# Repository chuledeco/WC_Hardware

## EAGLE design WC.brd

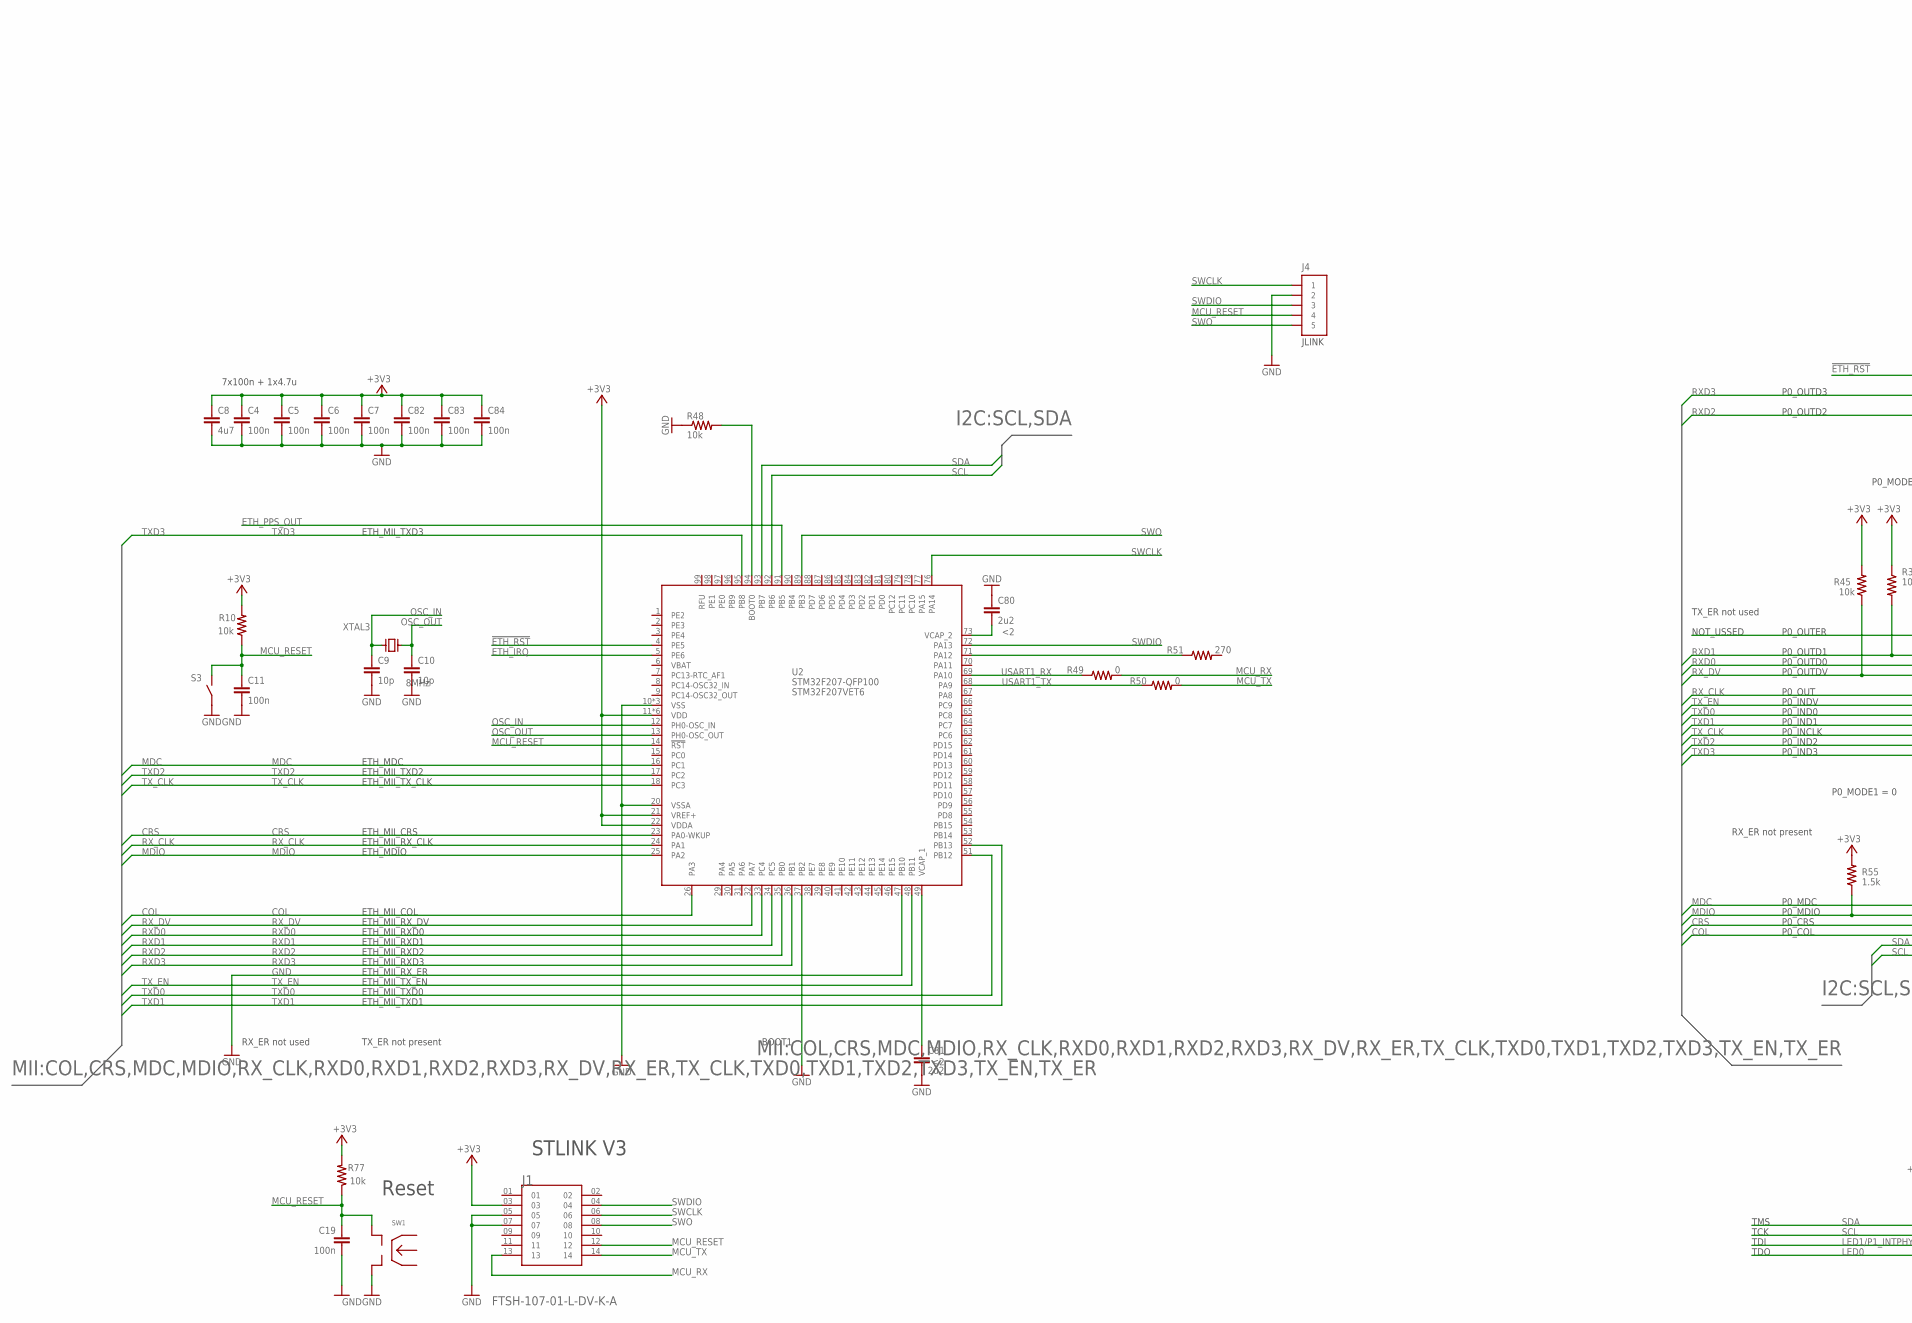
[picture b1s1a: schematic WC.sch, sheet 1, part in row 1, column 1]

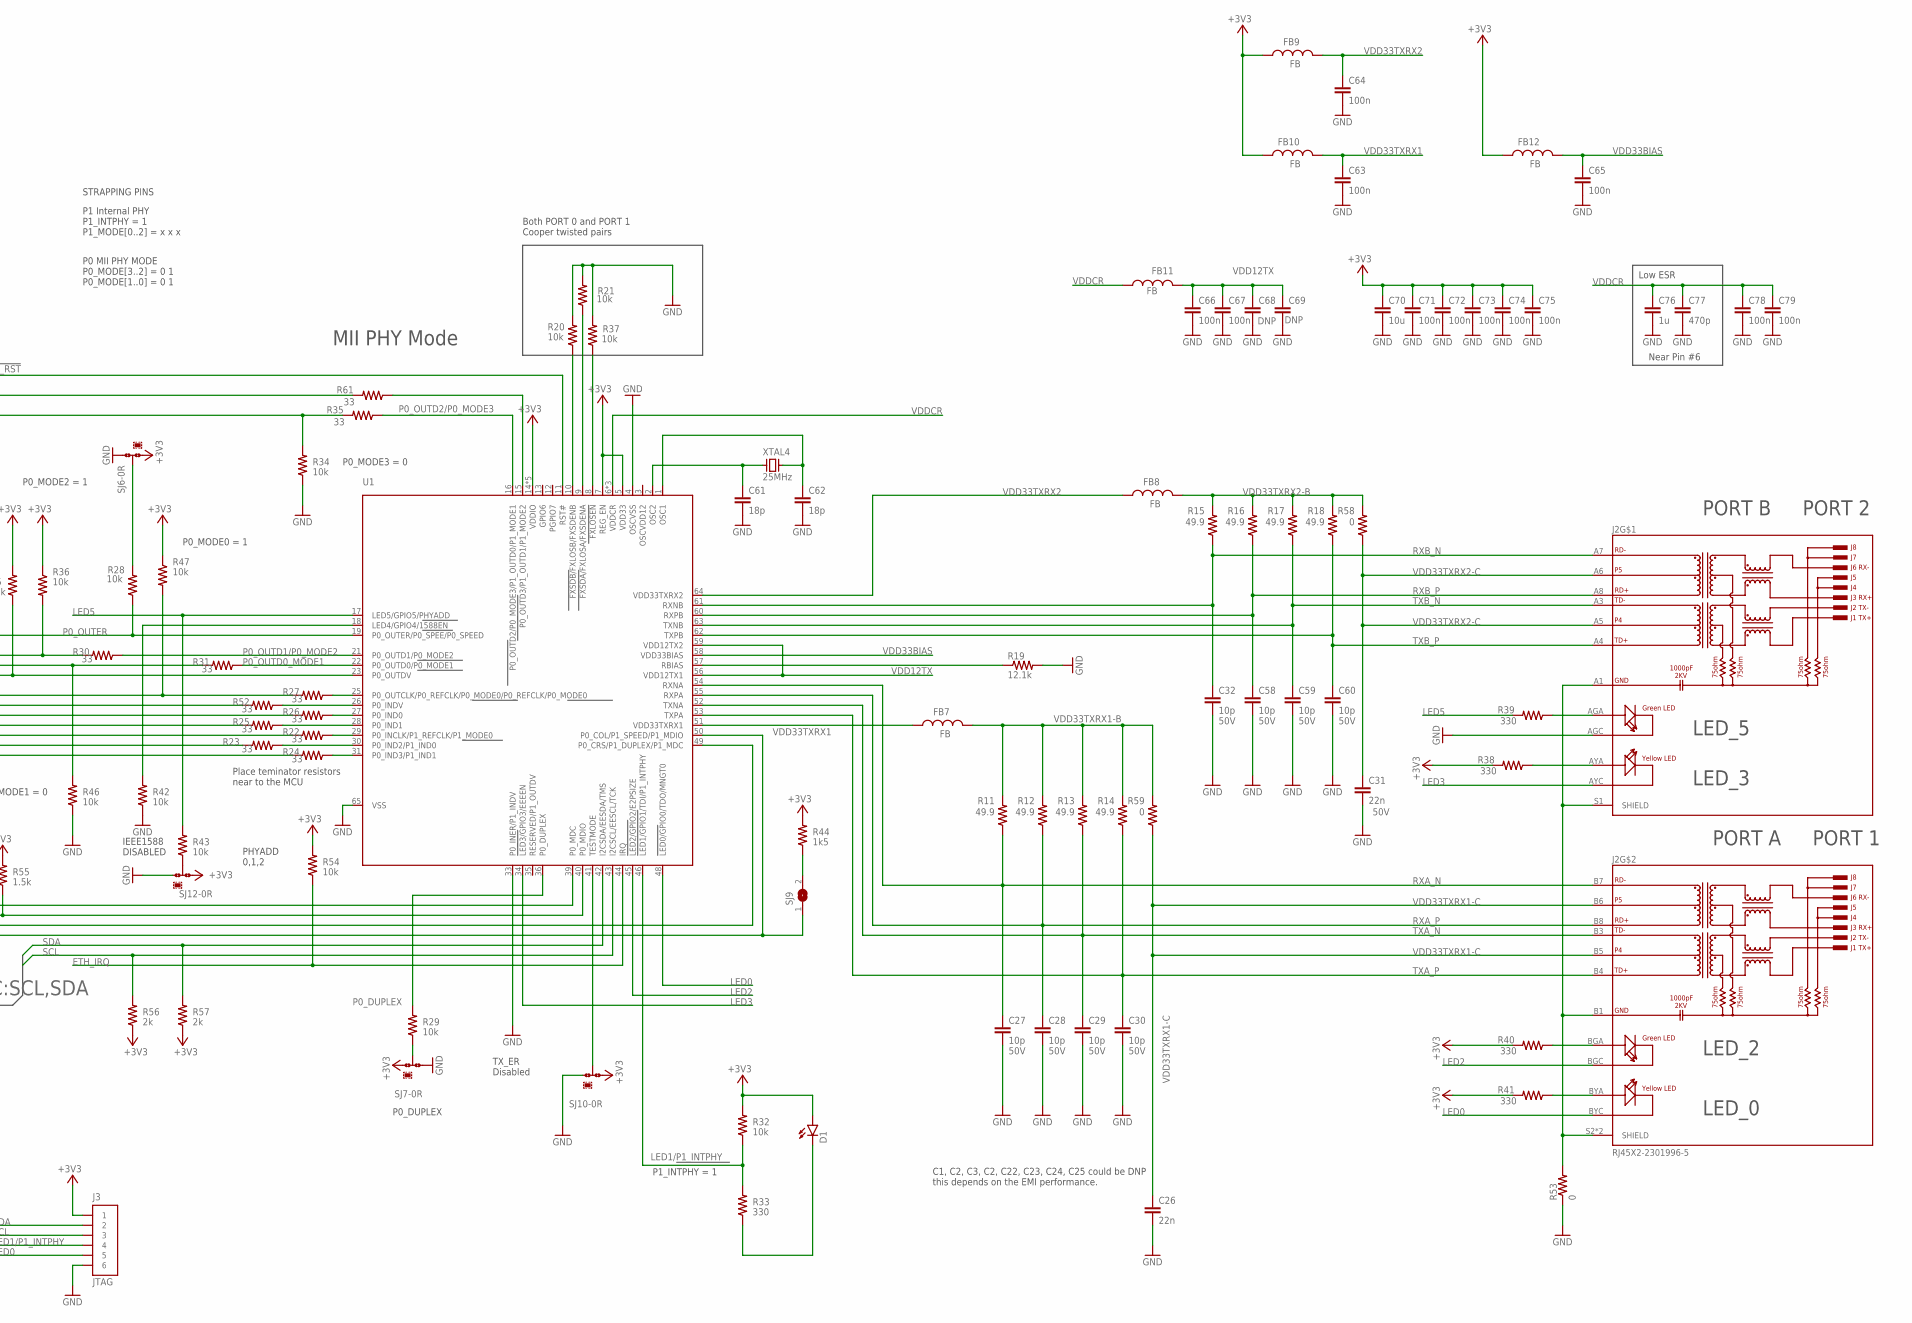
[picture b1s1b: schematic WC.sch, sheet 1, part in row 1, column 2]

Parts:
C4, C5, C6, C7, C11, C19, C63, C64, C65, C66, C67, C68, C69, C71, C72, C73, C74, C75, C78, C79, C82, C83, C84: 100n; C_0603
C8: 4u7; C_0805
C9, C10: 10p; C_0603
C26: 22n; C_0805
C27, C28, C29, C30, C32, C58, C59, C60: 10p; C_0402
C31: 22n; C_0805; VOLTAGE 50V
C61, C62: 18p; C_0603
C70: 10u; C_0603
C76: 1u; C_0603
C77: 470p; C_0603
C80, C81: 2u2; C_0603
D1: LED_0603_ARROW
FB7, FB8, FB9, FB10, FB11, FB12: FB; L_0603
J1: FTSH-107-01-L-DV-K-A; SAMTEC_FTSH-107-01-L-DV-K-A
J2: RJ45X2-2301996-5; 2301996-5
J3: JTAG; CONN-VERT-2.54MM-6PINS-2ROWS
J4: CONVERT-1X5-2.54MM-MALE_HOLES; 1X05
R10, R20, R21, R28, R29, R32, R34, R36, R37, R42, R43, R45, R46, R47, R48, R54, R77: 10k; R_0603
R11, R12, R13, R14, R15, R16, R17, R18: 49.9; R_0402
R19: 12.1k; R_0603
R22, R23, R24, R25, R26, R27, R30, R31, R35, R52, R61: 33; R_0603
R33, R38, R39, R40, R41: 330; R_0603
R44: 1k5; R_0603
R49, R50: 0; R_0603
R51: 270; R_0603
R53: 0; R_1206
R55: 1.5k; R_0603
R56, R57: 2k; R_0603
R58, R59: 0; R_0402
S3: TSWITCH_SMTR2; SMTR2
SJ6: attributre; A0R-JMP
SJ7, SJ10, SJ12: 0R-JUMPA; A0R-JMP
SJ9: SJ
SW1: SWITCH-SCREW; SCREW-SWITCH
U1: LAN9353; QFN50P900X900X100-65T600N
U2: STM32F207-QFP100; QFP50P1600X1600X160-100N; MPN STM32F207VET6
XTAL3: 8MHz; XTAL3.2X2.5; MPN 830108313809
XTAL4: 25MHz; XTAL3.2X2.5

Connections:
!ETH_RST!: U1.11 (RST#), U2.4 (PE5)
+3V3: C4.P$1 (1), C5.P$1 (1), C6.P$1 (1), C7.P$1 (1), C8.P$1 (1), C70.P$1 (1), C71.P$1 (1), C72.P$1 (1), C73.P$1 (1), C74.P$1 (1), C75.P$1 (1), C82.P$1 (1), C83.P$1 (1), C84.P$1 (1), D1.A, FB9.2, FB10.2, FB12.2, J1.03, J3.1, R10.2, R32.2, R36.1, R38.2, R40.2, R41.2, R44.2, R45.2, R47.1, R54.2, R55.2, R56.1, R57.1, R77.2, SJ6.1, SJ7.1, SJ10.3, SJ12.3, U1.5 (VDD33), U1.7 (REG_EN), U1.14 (VDDIO), U1.20 (VDDIO), U1.32 (VDDIO), U1.37 (VDDIO), U1.47 (VDDIO), U2.11 (VDD), U2.19 (VDD), U2.21 (VREF+), U2.22 (VDDA), U2.28 (VDD), U2.50 (VDD), U2.75 (VDD), U2.100 (VDD); also elsewhere on the board
COL: SJ9.1, U1.50 (P0_COL/P1_SPEED/P1_MDIO), U2.26 (PA3)
CRS: U1.49 (P0_CRS/P1_DUPLEX/P1_MDC), U2.23 (PA0-WKUP)
ETH_IRQ: R54.1, U1.44 (IRQ), U2.5 (PE6)
ETH_PPS_OUT: U2.91 (PB5)
GND: C4.P$2 (2), C5.P$2 (2), C6.P$2 (2), C7.P$2 (2), C8.P$2 (2), C9.P$2 (2), C10.P$2 (2), C11.P$2 (2), C19.P$2 (2), C26.P$2 (2), C27.P$2 (2), C28.P$2 (2), C29.P$2 (2), C30.P$2 (2), C31.P$2 (2), C32.P$2 (2), C58.P$2 (2), C59.P$2 (2), C60.P$2 (2), C61.P$2 (2), C62.P$2 (2), C63.P$2 (2), C64.P$2 (2), C65.P$2 (2), C66.P$2 (2), C67.P$2 (2), C68.P$2 (2), C69.P$2 (2), C70.P$2 (2), C71.P$2 (2), C72.P$2 (2), C73.P$2 (2), C74.P$2 (2), C75.P$2 (2), C76.P$2 (2), C77.P$2 (2), C78.P$2 (2), C79.P$2 (2), C80.P$1 (1), C81.P$2 (2), C82.P$2 (2), C83.P$2 (2), C84.P$2 (2), J1.05, J1.07, J2.AGC (GC), J3.6, J4.2, R19.2, R20.2, R21.2, R34.1, R37.2, R42.1, R46.1, R48.1, R53.1, S3.P$1, S3.P$2, SJ6.3, SJ7.3, SJ10.1, SJ12.1, SW1.2, U1.4 (OSCVSS), U1.33 (P0_INER/P1_INDV), U1.65 (VSS), U2.10 (VSS), U2.20 (VSSA), U2.27 (VSS), U2.37 (PB2), U2.47 (PB10), U2.74 (VSS); also elsewhere on the board
LED0: J2.BYC (YC), J3.5, U1.48 (LED0/GPIO0/TDO/MNGT0)
LED1/P1_INTPHY: J3.4, R32.1, R33.2, U1.46 (LED1/GPIO1/TDI/P1_INTPHY)
LED1_C1: D1.K, R33.1
LED2: J2.BGC (GC), U1.45 (LED2/GPIO2/E2PSIZE)
LED3: J2.AYC (YC), U1.34 (LED3/GPIO3/EEEEN)
LED5: R39.2, R43.2, U1.17 (LED5/GPIO5/PHYADD)
MCU_RESET: C11.P$1 (1), C19.P$1 (1), J1.12, J4.4, R10.1, R77.1, S3.P$3, S3.P$4, SW1.1, U2.14 (!RST!)
MCU_RX: J1.13, R49.2
MCU_TX: J1.14, R50.2
MDC: U1.39 (P0_MDC), U2.16 (PC1)
MDIO: R55.1, U1.40 (P0_MDIO), U2.25 (PA2)
unnamed: R43.1, SJ12.2
unnamed: C80.P$2 (2), U2.73 (VCAP_2)
unnamed: C81.P$1 (1), U2.49 (VCAP_1)
unnamed: R48.2, U2.94 (BOOT0)
unnamed: R51.1, U2.71 (PA12)
unnamed: C61.P$1 (1), U1.2 (OSC2), XTAL4.P$1 (X1)
unnamed: C62.P$1 (1), U1.1 (OSC1), XTAL4.P$3 (X2)
unnamed: R19.1, U1.57 (RBIAS)
unnamed: R20.1, U1.10 (FXSDB/FXLOSB/FXSDENB)
unnamed: R21.1, U1.9 (FXSDA/FXLOSA/FXSDENA)
unnamed: R22.1, U1.29 (P0_INCLK/P1_REFCLK/P1_MODE0)
unnamed: R23.1, U1.30 (P0_IND2/P1_IND0)
unnamed: R24.1, U1.31 (P0_IND3/P1_IND1)
unnamed: R27.1, U1.25 (P0_OUTCLK/P0_REFCLK/P0_MODE0/P0_REFCLK/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)
unnamed: R26.1, U1.27 (P0_IND0)
unnamed: R25.1, U1.28 (P0_IND1)
unnamed: R28.2, SJ6.2
unnamed: R29.1, SJ7.2
unnamed: R37.1, U1.8 (FXLOSEN)
unnamed: J2.AYA (YA), R38.1
unnamed: J2.AGA (GA), R39.1
unnamed: J2.BGA (GA), R40.1
unnamed: J2.BYA (YA), R41.1
unnamed: R42.2, U1.18 (LED4/GPIO4/1588EN)
unnamed: R44.1, SJ9.2
unnamed: SJ10.2, U1.41 (TESTMODE)
unnamed: R52.1, U1.26 (P0_INDV)
unnamed: R61.1, U1.15 (P0_OUTD3/P1_OUTD1/P1_MODE2)
OSC_IN: C9.P$1 (1), U2.12 (PH0-OSC_IN), XTAL3.P$3 (X2)
OSC_OUT: C10.P$1 (1), U2.13 (PH0-OSC_OUT), XTAL3.P$1 (X1)
P0_DUPLEX: R29.2, U1.36 (P0_DUPLEX)
P0_OUTD0_MODE1: R31.1, U1.22 (P0_OUTD0/P0_MODE1)
P0_OUTD1/P0_MODE2: R30.1, U1.21 (P0_OUTD1/P0_MODE2)
P0_OUTD2/P0_MODE3: R35.1, U1.16 (P0_OUTD2/P0_MODE3/P1_OUTD0/P1_MODE1)
P0_OUTER: R28.1, U1.19 (P0_OUTER/P0_SPEE/P0_SPEED)
RXA_N: C27.P$1 (1), J2.B7 (RD-), R11.1, U1.54 (RXNA)
RXA_P: C28.P$1 (1), J2.B8 (RD+), R12.1, U1.55 (RXPA)
RXB_N: C32.P$1 (1), J2.A7 (RD-), R15.1, U1.61 (RXNB)
RXB_P: C58.P$1 (1), J2.A8 (RD+), R16.1, U1.60 (RXPB)
RXD0: R31.2, R46.2, U2.33 (PC4)
RXD1: R30.2, R36.2, U2.34 (PC5)
RXD2: R34.2, R35.2, U2.35 (PB0)
RXD3: R61.2, U2.36 (PB1)
RX_CLK: R27.2, R47.2, U2.24 (PA1)
RX_DV: R45.1, U1.23 (P0_OUTDV), U2.32 (PA7)
SCL: J3.3, R56.2, U1.43 (I2CSCL/EESCL/TCK), U2.92 (PB6)
SDA: J3.2, R57.2, U1.42 (I2CSDA/EESDA/TMS), U2.93 (PB7)
SHIELD1: J2.A1 (GND), J2.B1 (GND), J2.S1 (SHIELD), J2.S2 (SHIELD), J2.S3 (SHIELD), R53.2
SWCLK: J1.06, J4.1, U2.76 (PA14)
SWDIO: J1.04, J4.3, U2.72 (PA13)
SWO: J1.08, J4.5, U2.89 (PB3)
TXA_N: C29.P$1 (1), J2.B3 (TD-), R13.1, U1.52 (TXNA)
TXA_P: C30.P$1 (1), J2.B4 (TD+), R14.1, U1.53 (TXPA)
TXB_N: C59.P$1 (1), J2.A3 (TD-), R17.1, U1.63 (TXNB)
TXB_P: C60.P$1 (1), J2.A4 (TD+), R18.1, U1.62 (TXPB)
TXD0: R26.2, U2.51 (PB12)
TXD1: R25.2, U2.52 (PB13)
TXD2: R23.2, U2.17 (PC2)
TXD3: R24.2, U2.95 (PB8)
TX_CLK: R22.2, U2.18 (PC3)
TX_EN: R52.2, U2.48 (PB11)
USART1_RX: R49.1, U2.69 (PA10)
USART1_TX: R50.1, U2.68 (PA9)
VDD12TX: C66.P$1 (1), C67.P$1 (1), C68.P$1 (1), C69.P$1 (1), FB11.2, U1.56 (VDD12TX1), U1.59 (VDD12TX2)
VDD33BIAS: C65.P$1 (1), FB12.1, U1.58 (VDD33BIAS)
VDD33TXRX1: C63.P$1 (1), FB7.2, FB10.1, U1.51 (VDD33TXRX1)
VDD33TXRX1-B: FB7.1, R11.2, R12.2, R13.2, R14.2, R59.2
VDD33TXRX1-C: C26.P$1 (1), J2.B5 (P4), J2.B6 (P5), R59.1
VDD33TXRX2: C64.P$1 (1), FB8.2, FB9.1, U1.64 (VDD33TXRX2)
VDD33TXRX2-B: FB8.1, R15.2, R16.2, R17.2, R18.2, R58.2
VDD33TXRX2-C: C31.P$1 (1), J2.A5 (P4), J2.A6 (P5), R58.1
VDDCR: C76.P$1 (1), C77.P$1 (1), C78.P$1 (1), C79.P$1 (1), FB11.1, U1.6 (VDDCR), U1.24 (VDDCR), U1.38 (VDDCR)

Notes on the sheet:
JLINK
ETH_MDC
ETH_MII_TXD2
ETH_MII_TX_CLK
ETH_MII_CRS
ETH_MII_RX_CLK
ETH_MDIO
ETH_MII_COL
ETH_MII_RX_DV
ETH_MII_RXD0
ETH_MII_RXD1
ETH_MII_RXD2
ETH_MII_RXD3
ETH_MII_RX_ER
ETH_MII_TX_EN
ETH_MII_TXD0
ETH_MII_TXD1
ETH_MII_TXD3
TX_ER not present
RX_ER not used
7x100n + 1x4.7u
BOOT1
Low ESR
P1 Internal PHY P1_INTPHY = 1 P1_MODE[0..2] = x x x
P0 MII PHY MODE P0_MODE[3..2] = 0 1 P0_MODE[1..0] = 0 1
STRAPPING PINS
P0_MODE3 = 0
P0_MODE2 = 1
P1_INTPHY = 1
PORT B
PORT A
PORT 1
PORT 2
LED_2
LED_0
LED_5
LED_3
Both PORT 0 and PORT 1 Cooper twisted pairs
IEEE1588 DISABLED
PHYADD 0,1,2

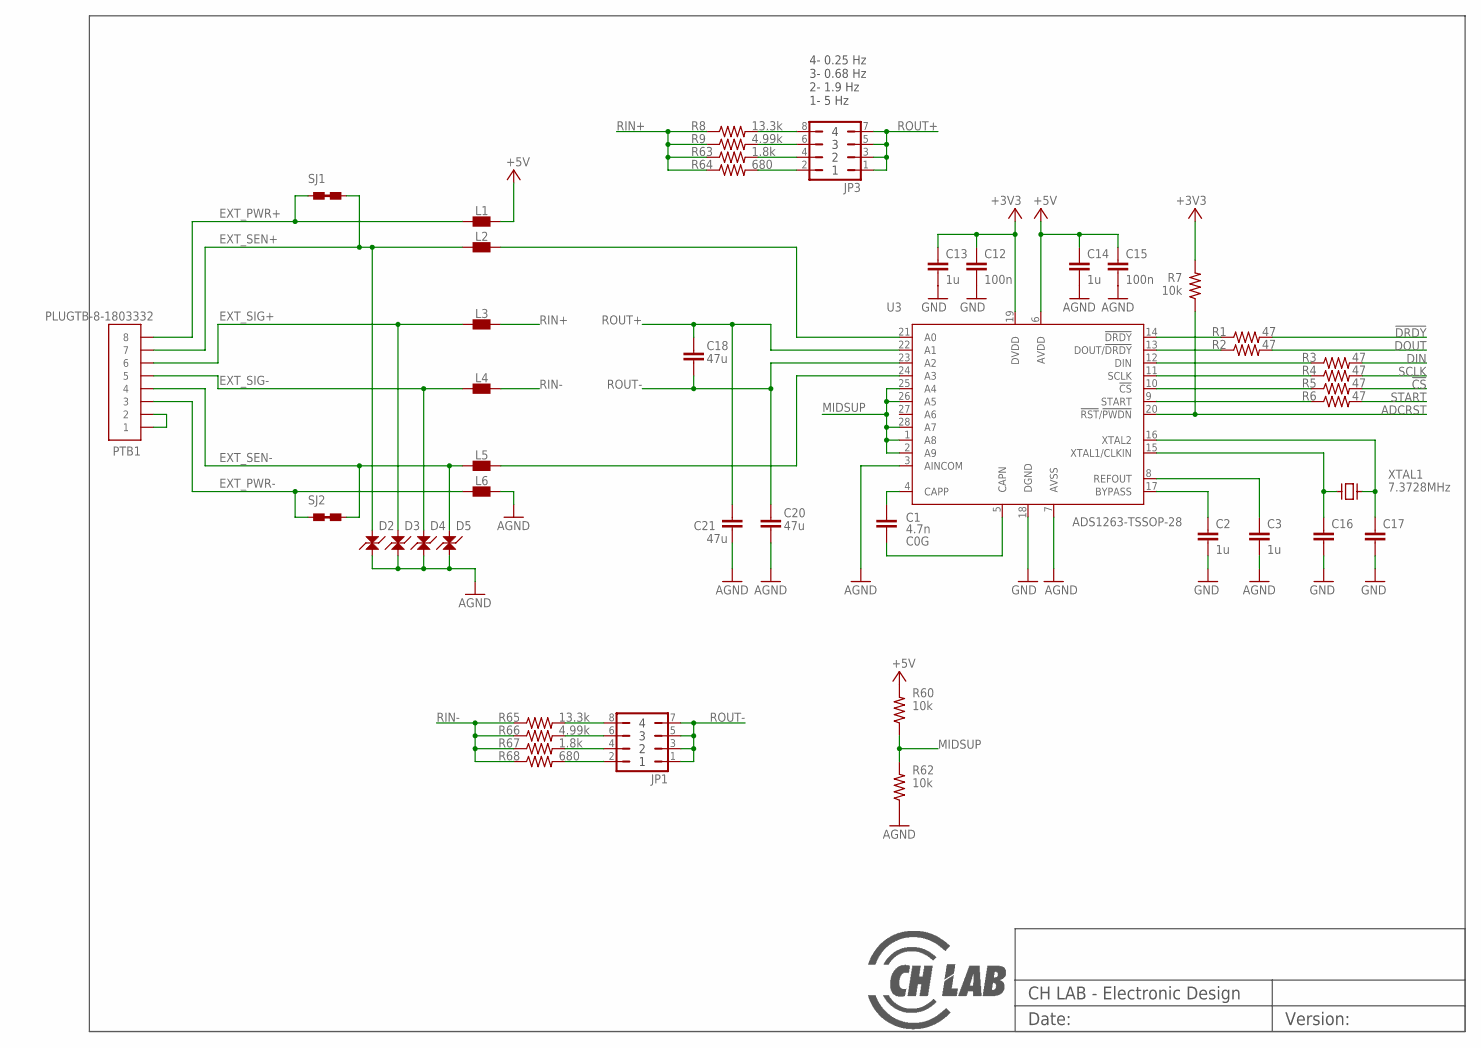
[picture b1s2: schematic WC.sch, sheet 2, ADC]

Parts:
C1: 4.7n; C_0603
C2, C3, C13, C14: 1u; C_0603
C12, C15: 100n; C_0603
C16, C17: C_0603
C18, C20, C21: 47u; C_1210
D2, D3, D4, D5: LESD5D5.0CT1G; SOD523
JP1, JP3: JP4Q
L1, L2, L3, L4, L5, L6: FB_0603; R_0603
PTB1: PLUGTB-8-1803332; 1803332
R1, R2, R3, R4, R5, R6: 47; R_0402
R7, R60, R62: 10k; R_0603
R8, R65: 13.3k; R_0603
R9, R66: 4.99k; R_0603
R63, R67: 1.8k; R_0603
R64, R68: 680; R_0603
SJ1, SJ2: SJUMPER-NC; SJ1
U3: ADS1263-TSSOP-28; SOP65P640X120-28N
XTAL1: 7.3728MHz; XTAL; MPN ABLS-7.3728MHZ-K4T

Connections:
!CS!: R5.2
!DRDY!: R1.2
+3V3: C12.P$1 (1), C13.P$1 (1), R7.2, U3.19 (DVDD); also elsewhere on the board
+5V: C14.P$1 (1), C15.P$1 (1), L1.2, R60.2, U3.6 (AVDD)
ADCRST: R7.1, U3.20 (!RST!/!PWDN!)
AGND: C3.P$2 (2), C14.P$2 (2), C15.P$2 (2), C20.P$1 (1), C21.P$1 (1), D2.C, D3.C, D4.C, D5.C, L6.2, R62.1, U3.3 (AINCOM), U3.7 (AVSS)
DIN: R3.2
DOUT: R2.2
EXT_PWR+: L1.1, PTB1.P$8 (8), SJ1.P$1
EXT_PWR-: L6.1, PTB1.P$3 (3), SJ2.P$1
EXT_SEN+: D2.A, L2.1, PTB1.P$7 (7), SJ1.P$2
EXT_SEN-: D5.A, L5.1, PTB1.P$4 (4), SJ2.P$2
EXT_SIG+: D3.A, L3.1, PTB1.P$6 (6)
EXT_SIG-: D4.A, L4.1, PTB1.P$5 (5)
GND: C2.P$2 (2), C12.P$2 (2), C13.P$2 (2), C16.P$2 (2), C17.P$2 (2), U3.18 (DGND); also elsewhere on the board
MIDSUP: R60.1, R62.2, U3.1 (A8), U3.2 (A9), U3.25 (A4), U3.26 (A5), U3.28 (A7)
unnamed: C1.P$2 (2), U3.5 (CAPN)
unnamed: C1.P$1 (1), U3.4 (CAPP)
unnamed: C2.P$1 (1), U3.17 (BYPASS)
unnamed: C3.P$1 (1), U3.8 (REFOUT)
unnamed: C17.P$1 (1), U3.16 (XTAL2), XTAL1.2 (X2)
unnamed: R3.1, U3.12 (DIN)
unnamed: R4.1, U3.11 (SCLK)
unnamed: R5.1, U3.10 (!CS!)
unnamed: R6.1, U3.9 (START)
unnamed: R1.1, U3.14 (!DRDY!)
unnamed: R2.1, U3.13 (DOUT/!DRDY!)
unnamed: C16.P$1 (1), U3.15 (XTAL1/CLKIN), XTAL1.1 (X1)
unnamed: L2.2, U3.21 (A0)
unnamed: JP3.8, R8.2
unnamed: JP3.6, R9.2
unnamed: JP3.4, R63.2
unnamed: JP3.2, R64.2
unnamed: L5.2, U3.24 (A3)
unnamed: JP1.8, R65.2
unnamed: JP1.6, R66.2
unnamed: JP1.4, R67.2
unnamed: JP1.2, R68.2
unnamed: PTB1.P$1 (1), PTB1.P$2 (2)
RIN+: L3.2, R8.1, R9.1, R63.1, R64.1
RIN-: L4.2, R65.1, R66.1, R67.1, R68.1
ROUT+: C18.P$1 (1), C21.P$2 (2), JP3.1, JP3.3, JP3.5, JP3.7, U3.22 (A1)
ROUT-: C18.P$2 (2), C20.P$2 (2), JP1.1, JP1.3, JP1.5, JP1.7, U3.23 (A2)
SCLK: R4.2
START: R6.2

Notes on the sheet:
4- 0.25 Hz 3- 0.68 Hz 2- 1.9 Hz 1- 5 Hz

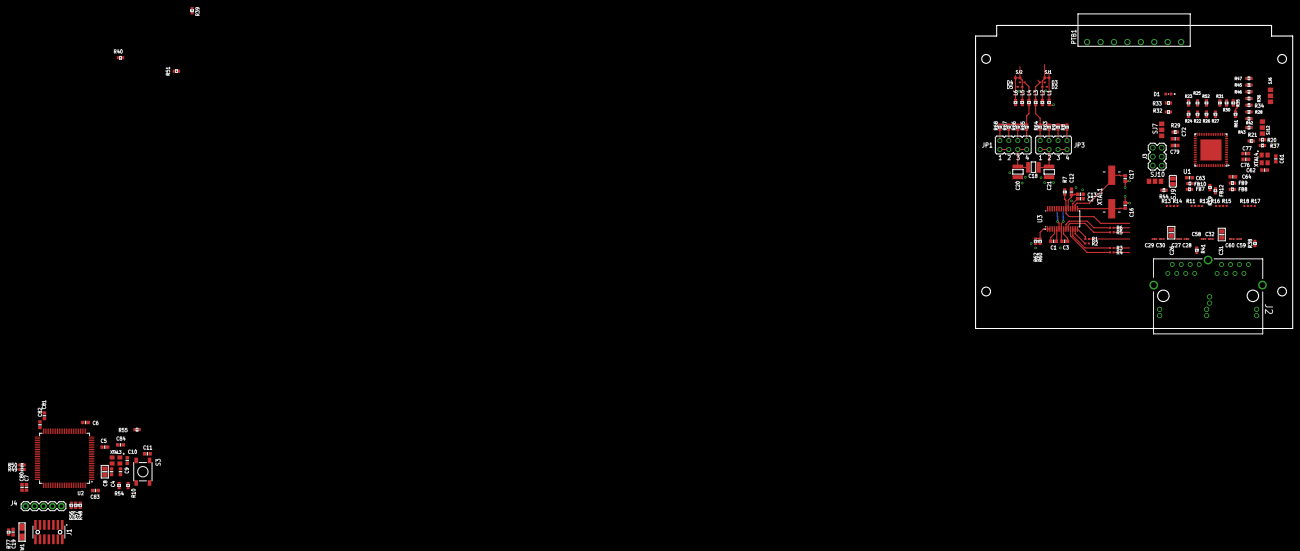
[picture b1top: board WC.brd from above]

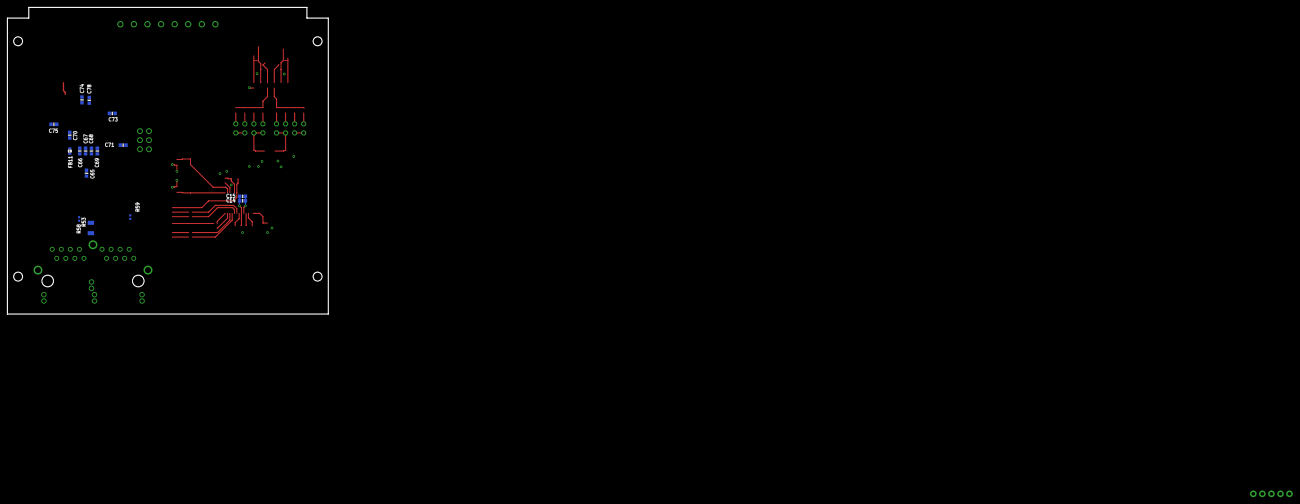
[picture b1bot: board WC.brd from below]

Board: 2 copper layers, 90.0 x 86.0 mm, 163 parts (17 on the bottom side), 126 nets.

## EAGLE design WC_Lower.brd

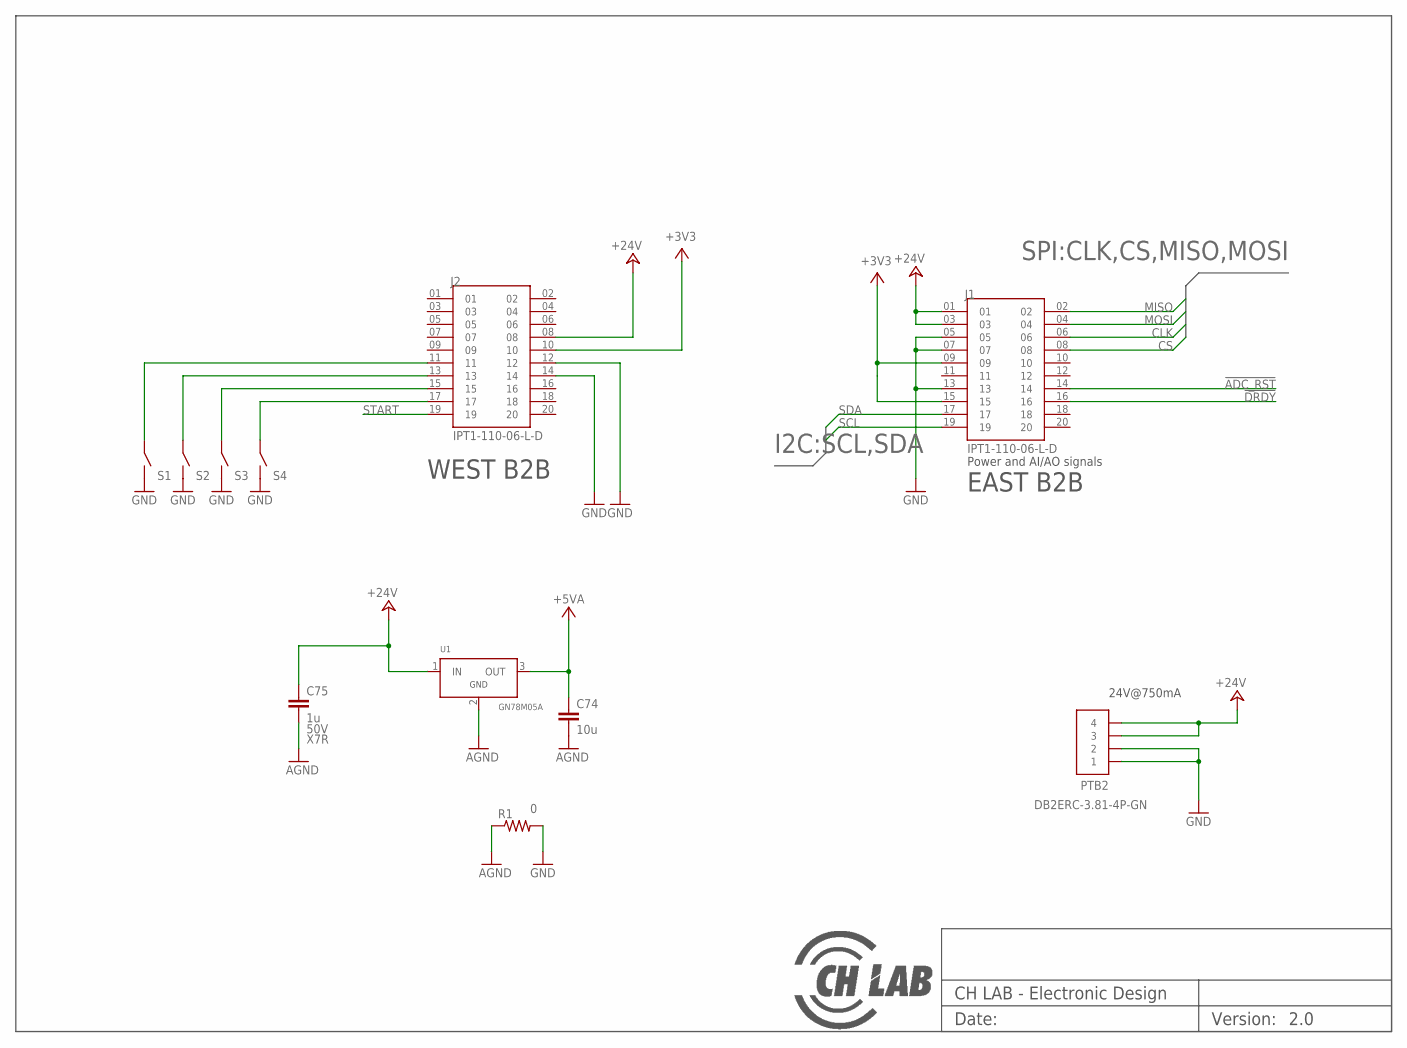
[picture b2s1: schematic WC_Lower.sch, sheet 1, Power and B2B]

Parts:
C74: 10u; C_0805
C75: 1u; C_1206
J1, J2: IPT1-110-06-L-D; SAMTEC_IPT1-110-06-L-D
PTB2: DB2ERC-3.81-4P-GN; 1803293
R1: 0; R_0603
S1, S2, S3, S4: TSWITCH_SMTR2; SMTR2
U1: GN78M05A; TO-252

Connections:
!ADC_RST!: J1.14; also elsewhere on the board
!DRDY!: J1.16; also elsewhere on the board
+3V3: J1.09, J1.15, J2.10; also elsewhere on the board
+5VA: C74.P$1 (1), U1.3 (OUT); also elsewhere on the board
+24V: C75.P$1 (1), J1.01, J1.03, J2.08, PTB2.P$3 (3), PTB2.P$4 (4), U1.1 (IN)
AGND: C74.P$2 (2), C75.P$2 (2), R1.1, U1.2 (GND); also elsewhere on the board
CLK: J1.06; also elsewhere on the board
CS: J1.08; also elsewhere on the board
GND: J1.05, J1.07, J1.13, J2.12, J2.14, PTB2.P$1 (1), PTB2.P$2 (2), R1.2, S1.P$3, S1.P$4, S2.P$3, S2.P$4, S3.P$3, S3.P$4, S4.P$3, S4.P$4; also elsewhere on the board
MISO: J1.02; also elsewhere on the board
MOSI: J1.04; also elsewhere on the board
unnamed: J2.17, S4.P$1, S4.P$2
unnamed: J2.15, S3.P$1, S3.P$2
unnamed: J2.13, S2.P$1, S2.P$2
unnamed: J2.11, S1.P$1, S1.P$2
SCL: J1.19
SDA: J1.17
START: J2.19; also elsewhere on the board

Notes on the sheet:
24V@750mA
EAST B2B
WEST B2B
Power and AI/AO signals

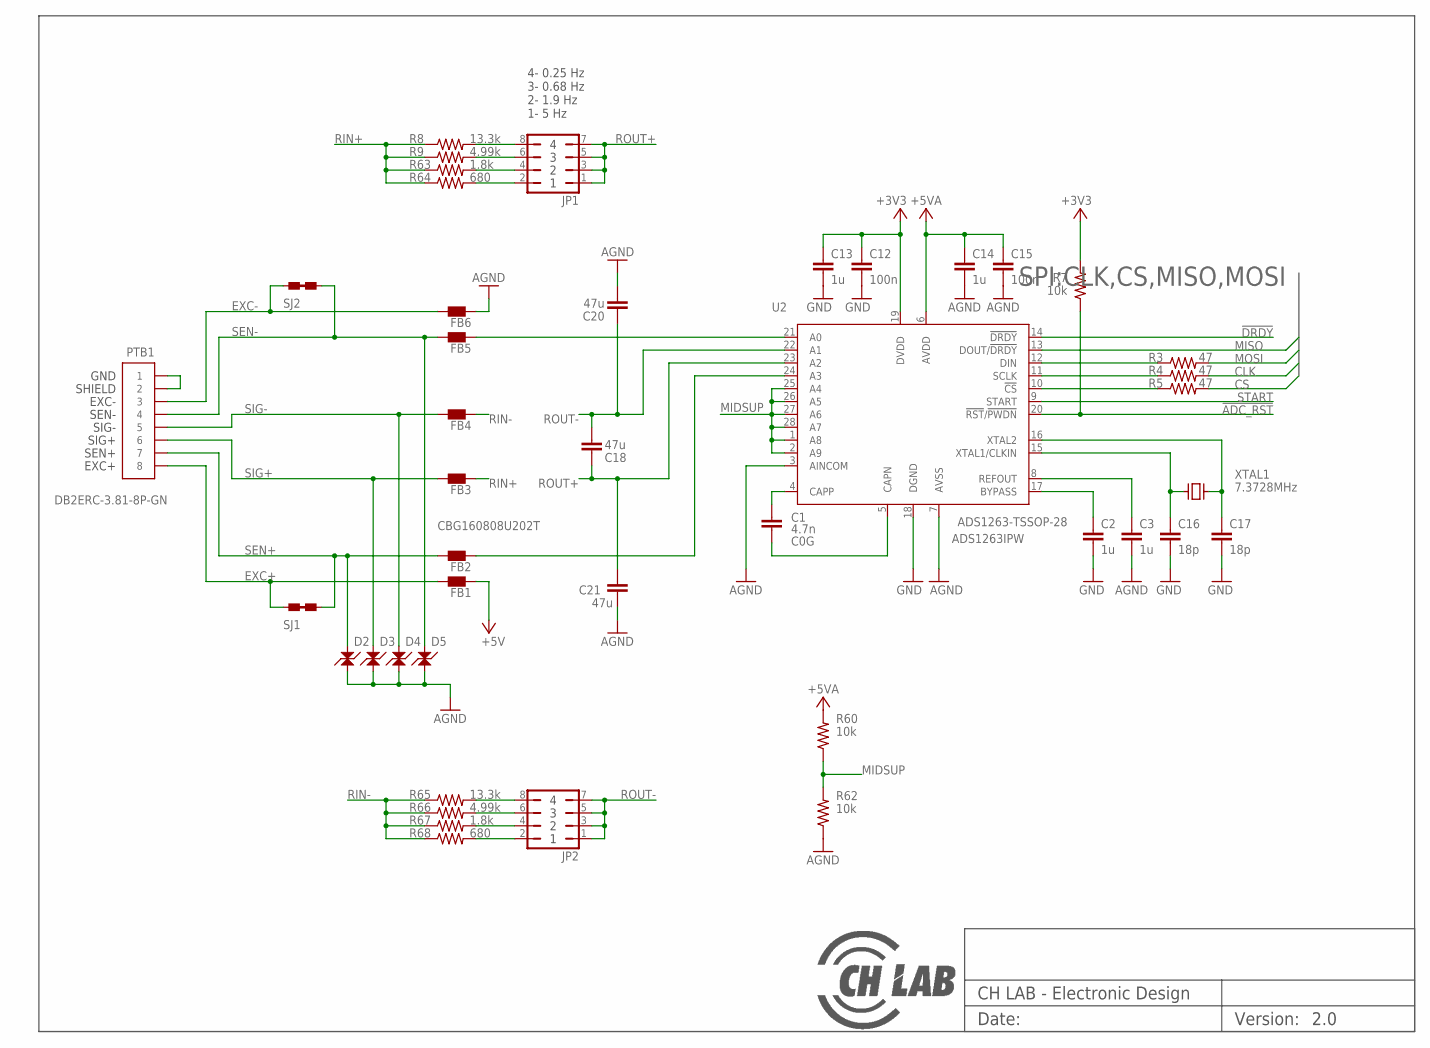
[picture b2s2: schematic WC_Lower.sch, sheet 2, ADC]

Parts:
C1: 4.7n; C_0603
C2, C3, C13, C14: 1u; C_0603
C12, C15: 100n; C_0603
C16, C17: 18p; C_0603
C18, C20, C21: 47u; C_1210
D2, D3, D4, D5: LESD5D5.0CT1G; SOD523
FB1, FB2, FB3, FB4, FB5, FB6: FB_0603; R_0603
JP1, JP2: CONVERT-2X4-2.54MALE; CONN-VERT-2.54MM-2X4-MALE
PTB1: DB2ERC-3.81-8P-GN; 1803332
R3, R4, R5: 47; R_0402
R7, R60, R62: 10k; R_0603
R8, R65: 13.3k; R_0603
R9, R66: 4.99k; R_0603
R63, R67: 1.8k; R_0603
R64, R68: 680; R_0603
SJ1, SJ2: SJUMPER-NC; SJ1
U2: ADS1263-TSSOP-28; SOP65P640X120-28N; MPN ADS1263IPW
XTAL1: 7.3728MHz; XTAL; MPN ABLS-7.3728MHZ-K4T

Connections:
!ADC_RST!: R7.1, U2.20 (!RST!/!PWDN!); also elsewhere on the board
!DRDY!: U2.14 (!DRDY!); also elsewhere on the board
+3V3: C12.P$1 (1), C13.P$1 (1), R7.2, U2.19 (DVDD); also elsewhere on the board
+5V: FB1.2
+5VA: C14.P$1 (1), C15.P$1 (1), R60.2, U2.6 (AVDD); also elsewhere on the board
AGND: C3.P$2 (2), C14.P$2 (2), C15.P$2 (2), C20.P$1 (1), C21.P$1 (1), D2.C, D3.C, D4.C, D5.C, FB6.2, R62.1, U2.3 (AINCOM), U2.7 (AVSS); also elsewhere on the board
CLK: R4.2; also elsewhere on the board
CS: R5.2; also elsewhere on the board
EXC+: FB1.1, PTB1.P$8 (8), SJ1.P$1
EXC-: FB6.1, PTB1.P$3 (3), SJ2.P$1
GND: C2.P$2 (2), C12.P$2 (2), C13.P$2 (2), C16.P$2 (2), C17.P$2 (2), U2.18 (DGND); also elsewhere on the board
MIDSUP: R60.1, R62.2, U2.1 (A8), U2.2 (A9), U2.25 (A4), U2.26 (A5), U2.27 (A6), U2.28 (A7)
MISO: U2.13 (DOUT/!DRDY!); also elsewhere on the board
MOSI: R3.2; also elsewhere on the board
unnamed: C1.P$2 (2), U2.5 (CAPN)
unnamed: C1.P$1 (1), U2.4 (CAPP)
unnamed: C2.P$1 (1), U2.17 (BYPASS)
unnamed: C3.P$1 (1), U2.8 (REFOUT)
unnamed: C17.P$1 (1), U2.16 (XTAL2), XTAL1.2 (X2)
unnamed: R3.1, U2.12 (DIN)
unnamed: PTB1.P$1 (1), PTB1.P$2 (2)
unnamed: R4.1, U2.11 (SCLK)
unnamed: R5.1, U2.10 (!CS!)
unnamed: C16.P$1 (1), U2.15 (XTAL1/CLKIN), XTAL1.1 (X1)
unnamed: FB2.2, U2.24 (A3)
unnamed: JP1.8, R8.2
unnamed: JP1.6, R9.2
unnamed: JP1.4, R63.2
unnamed: JP1.2, R64.2
unnamed: FB5.2, U2.21 (A0)
unnamed: JP2.8, R65.2
unnamed: JP2.6, R66.2
unnamed: JP2.4, R67.2
unnamed: JP2.2, R68.2
RIN+: FB3.2, R8.1, R9.1, R63.1, R64.1
RIN-: FB4.2, R65.1, R66.1, R67.1, R68.1
ROUT+: C18.P$1 (1), C21.P$2 (2), JP1.1, JP1.3, JP1.5, JP1.7, U2.23 (A2)
ROUT-: C18.P$2 (2), C20.P$2 (2), JP2.1, JP2.3, JP2.5, JP2.7, U2.22 (A1)
SEN+: D2.A, FB2.1, PTB1.P$7 (7), SJ1.P$2
SEN-: D5.A, FB5.1, PTB1.P$4 (4), SJ2.P$2
SIG+: D3.A, FB3.1, PTB1.P$6 (6)
SIG-: D4.A, FB4.1, PTB1.P$5 (5)
START: U2.9 (START); also elsewhere on the board

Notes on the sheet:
4- 0.25 Hz 3- 0.68 Hz 2- 1.9 Hz 1- 5 Hz
GND
SHIELD
EXC-
SEN-
SIG-
SIG+
SEN+
EXC+
CBG160808U202T

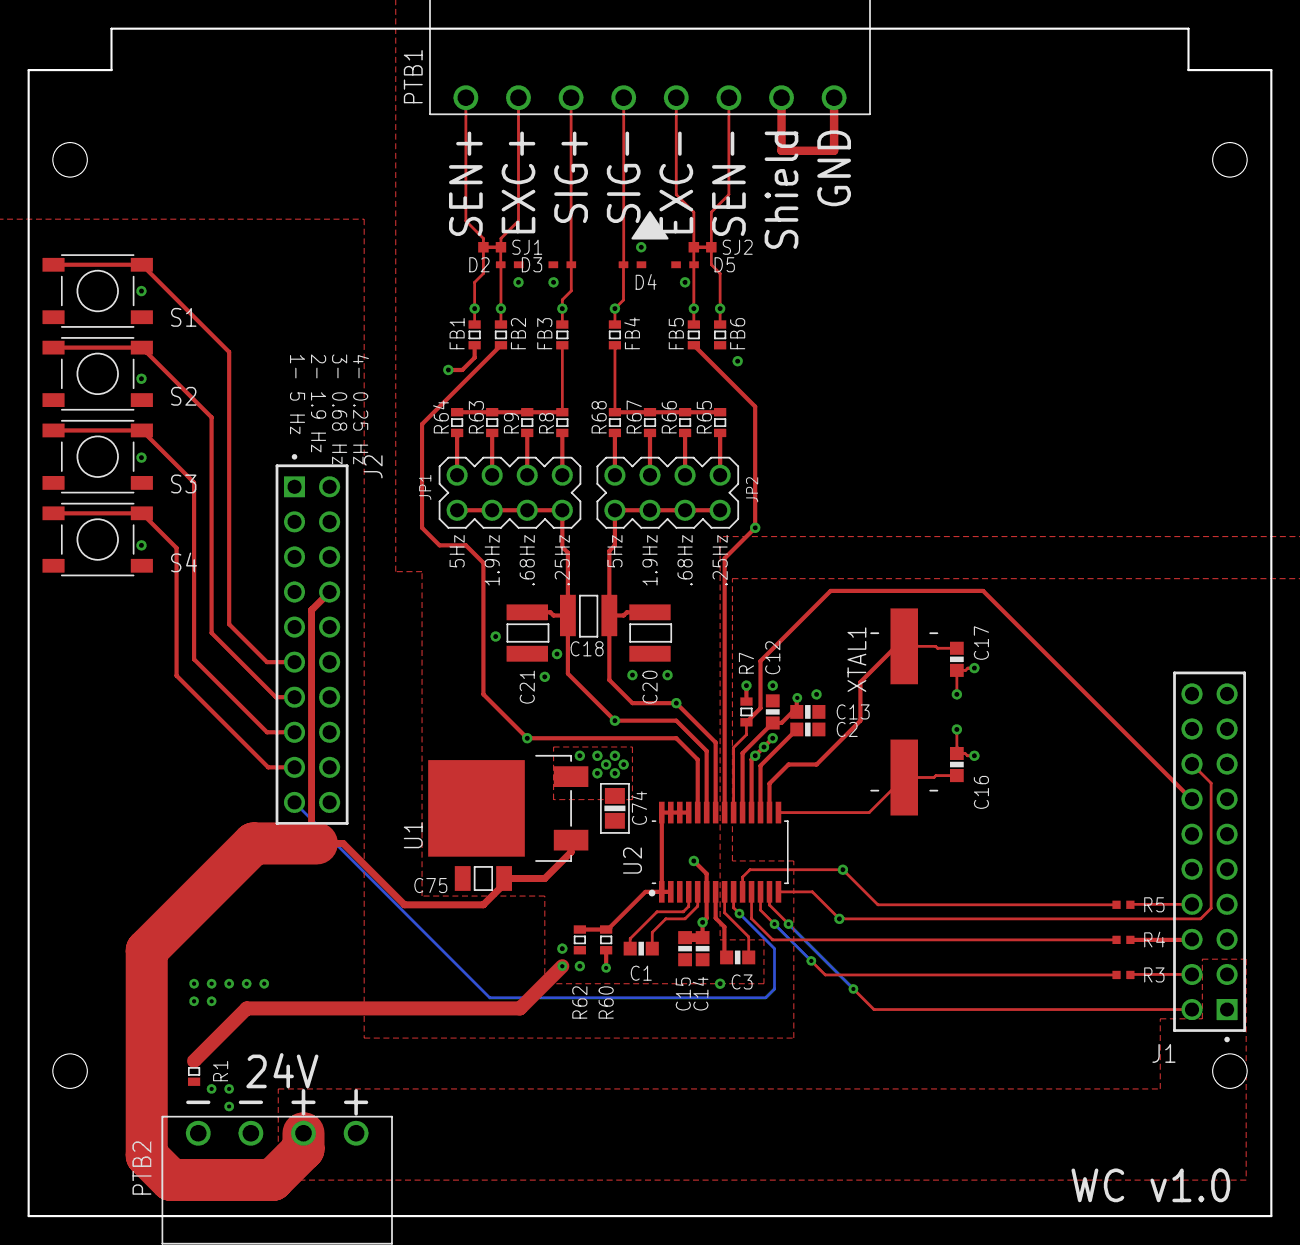
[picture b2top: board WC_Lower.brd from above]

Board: 4 copper layers, 90.0 x 86.0 mm, 54 parts (0 on the bottom side), 47 nets.

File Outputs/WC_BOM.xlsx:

Qty | Parts | Value | Device | Package | Sensitive | MPN | LINK
1 | C1 | 4.7n | C_0603 | C_0603 | NO | 0603B472K500NT | https://www.lcsc.com/product-detail/Multilayer-Ceramic-Capac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
2 | C12, C15 | 100n | C_0603 | C_0603 | NO | 0603F104M500NT | https://www.lcsc.com/product-detail/Multilayer-Ceramic-Capac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
2 | C16, C17 | 20pf | C_0603 | C_0603 | NO | CC0603JRNPO9BN200 | https://www.lcsc.com/product-detail/Multilayer-Ceramic-Capac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
3 | C18, C20, C21 | 47u | C_1210 | C_1210 | NO | CS3225X5R476K160NRL | https://www.lcsc.com/product-detail/Multilayer-Ceramic-Capac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
4 | C2, C3, C13, C14 | 1u | C_0603 | C_0603 | NO | CL10A105KO8NNNC | https://www.lcsc.com/product-detail/Multilayer-Ceramic-Capac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
1 | C74 | 10u | C_0805 | C_0805 | NO | CL21B106KOQNNNE | https://www.lcsc.com/product-detail/Multilayer-Ceramic-Capac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
1 | C75 | 1u x 50V | C_1206 | C_1206 | NO | CL31B105KBHNNNE | https://www.lcsc.com/product-detail/Multilayer-Ceramic-Capac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
1 | R1 | 0 | R_0603 | R_0603 | NO | 0603WAF0000T5E | https://www.lcsc.com/product-detail/Chip-Resistor-Surface-Mo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
3 | R3, R4, R5 | 47 | R_0402 | R_0402 | NO | 0402WGF470JTCE | https://www.lcsc.com/product-detail/Chip-Resistor-Surface-Mo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
2 | R63, R67 | 1.8k | R_0603 | R_0603 | NO | 0603WAF1801T5E | https://www.lcsc.com/product-detail/Chip-Resistor-Surface-Mo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
2 | R64, R68 | 680 | R_0603 | R_0603 | NO | 0603WAF6800T5E | https://www.lcsc.com/product-detail/Chip-Resistor-Surface-Mo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
3 | R7, R60, R62 | 10k | R_0603 | R_0603 | NO | 0603WAF1002T5E | https://www.lcsc.com/product-detail/Chip-Resistor-Surface-Mo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
2 | R8, R65 | 13.3k | R_0603 | R_0603 | NO | 0603WAF1332T5E | https://www.lcsc.com/product-detail/Chip-Resistor-Surface-Mo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
2 | R9, R66 | 4.99k | R_0603 | R_0603 | NO | 0603WAF4991T5E | https://www.lcsc.com/product-detail/Chip-Resistor-Surface-Mo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
6 | FB1, FB2, FB3, FB4, FB5, FB6 | FB | L_0603 | L_0603 | NO | CBG160808U202T | https://www.lcsc.com/product-detail/Ferrite-Beads_FH-Guangdo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
4 | D2, D3, D4, D5 | - | LESD5D5.0CT1G | SOD523 | NO | LESD5D5.0CT1G | https://www.lcsc.com/product-detail/Diodes-ESD_LRC-LESD5D5-0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
1 | U1 | 5V | Linear regulator | TO-252 | YES | GN78M05A | https://www.lcsc.com/product-detail/Linear-Voltage-Regulator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
1 | U2 | 32bits 38kSPS | ADC | TSSOP-28 | YES | ADS1263IPW | https://www.digikey.com/en/products/detail/texas-instruments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
4 | S1, S2, S3, S4 | SPST | Tswitch | SMTR2 | NO | PTS525SM15SMTR2LFS | https://www.lcsc.com/product-detail/Tactile-Switches_C-K-PTS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
1 | XTAL1 | 7.3728MHz | XTAL_11.4X4.7 | XTAL | YES | ABLS-7.3728MHZ-K4T | https://www.mouser.com/ProductDetail/ABRACON/ABLS-7.3728MHZ-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
2 | J1, J2 | IPT1-110-06-L-D | IPT1-110-06-L-D | SAMTEC_IPT1-110-06-L-D | NO | IPT1-110-06-L-D | https://www.digikey.com/short/j798b222
2 | JP1, JP2 |  | JP4Q | JP4Q | NO | PZ254V-12-8P | https://www.lcsc.com/product-detail/Pin-Headers_XFCN-PZ254V-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
2 | JJMP1, JMP2 | 2x2,54mm | Jumper |  | NO | 881545-2 | https://www.lcsc.com/product-detail/Shunts-Jumpers_TE-Connec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
1 | PTB1 | 20 positions | PLUG TB | P=3,81mm | NO | DB2ERC-3.81-20P-GN | https://www.lcsc.com/product-detail/Pluggable-System-Termina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
1 | PTB2 | 4 positions | PLUG TB | P=3,81mm | NO | DB2ERC-3.81-4P-GN | https://www.lcsc.com/product-detail/Pluggable-System-Termina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
1 | P1 | For DB2ERC-3.81-4P-GN | Jack TB |  | NO | DB2EK-3.81-4P-GN-S | https://www.lcsc.com/product-detail/Pluggable-System-Termina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
1 | P2 | For DB2ERC-3.81-20P-GN | Jack TB |  | NO | DB2EK-3.81-20P-GN-S | https://www.lcsc.com/product-detail/Pluggable-System-Termina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

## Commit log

2024-03-19 Primer commit
